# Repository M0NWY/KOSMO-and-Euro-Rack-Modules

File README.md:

# KOSMO-and-Euro-Rack-Modules
A backup place for my module designs / build instructions.

555 Techno Kick modules and or PCB and Panels available here : https://www.etsy.com/uk/shop/NewysModules

Demo video here :  https://youtu.be/yIHIAyrZvMU

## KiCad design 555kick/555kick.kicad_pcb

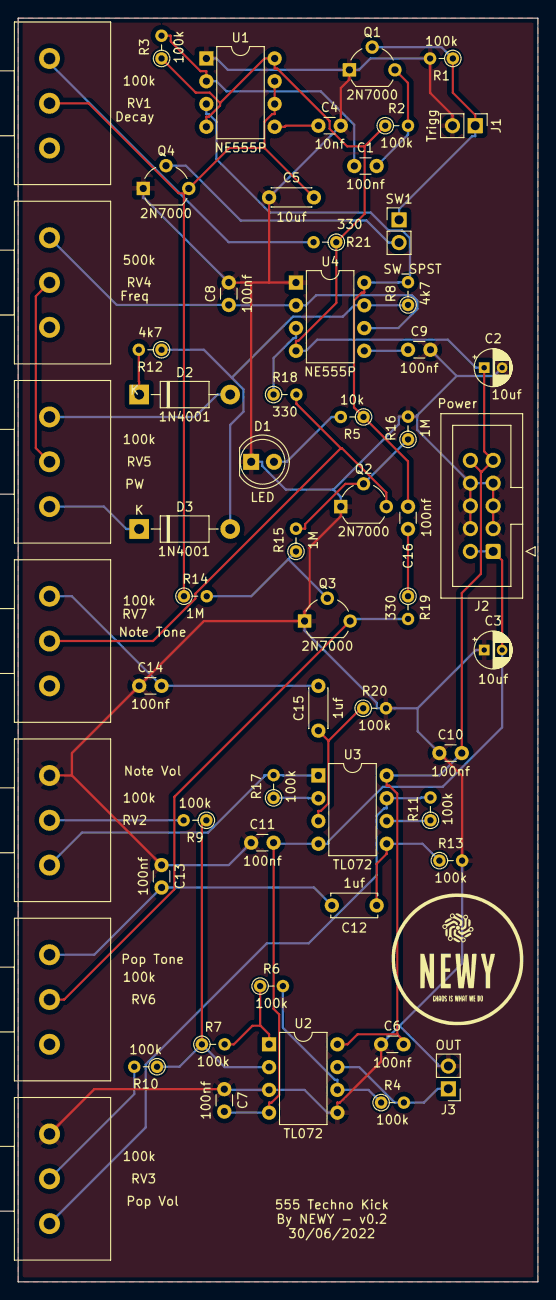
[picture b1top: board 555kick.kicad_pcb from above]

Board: 2 copper layers, 58.0 x 141.0 mm, 59 parts (0 on the bottom side), 39 nets.

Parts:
C1, C6, C7, C8, C9, C10, C11, C13, C14, C16: 100nf; C_Disc_D3.0mm_W1.6mm_P2.50mm
C2, C3: 10uf; CP_Radial_D4.0mm_P2.00mm
C4: 10nf; C_Disc_D3.0mm_W1.6mm_P2.50mm
C5: 10uf; C_Disc_D4.3mm_W1.9mm_P5.00mm
C12: 1uf; C_Disc_D5.0mm_W2.5mm_P5.00mm
C15: 1uf; C_Disc_D4.3mm_W1.9mm_P5.00mm
D1: LED; LED_D5.0mm
D2, D3: 1N4001; D_DO-41_SOD81_P10.16mm_Horizontal
J1: Trigg; PinHeader_1x02_P2.54mm_Vertical
J2: Power; IDC-Header_2x05_P2.54mm_Vertical
J3: OUT; PinHeader_1x02_P2.54mm_Vertical
Q1, Q2, Q3, Q4: 2N7000; TO-92_Wide
R1, R2, R3, R4, R6, R7, R9, R10, R11, R13, R17, R20: 100k; R_Axial_DIN0204_L3.6mm_D1.6mm_P2.54mm_Vertical
R5: 10k; R_Axial_DIN0204_L3.6mm_D1.6mm_P2.54mm_Vertical
R8, R12: 4k7; R_Axial_DIN0204_L3.6mm_D1.6mm_P2.54mm_Vertical
R14, R15, R16: 1M; R_Axial_DIN0204_L3.6mm_D1.6mm_P2.54mm_Vertical
R18, R19, R21: 330; R_Axial_DIN0204_L3.6mm_D1.6mm_P2.54mm_Vertical
RV1, RV2, RV3, RV5, RV6, RV7: 100k; Potentiometer_Alps_RK163_Single_Horizontal
RV4: 500k; Potentiometer_Alps_RK163_Single_Horizontal
SW1: SW_SPST; PinHeader_1x02_P2.54mm_Vertical
U1, U4: NE555P; DIP-8_W7.62mm
U2, U3: TL072; DIP-8_W7.62mm

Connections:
+12V: C2.1, C6.2, C10.2, J2.9, J2.10, R2.1, R3.1, R21.1, U1.4 (R), U1.8 (VCC), U2.8 (V+), U3.8 (V+), U4.4 (R)
-12V: C3.2, C7.2, C11.2, J2.1, J2.2, U2.4 (V-), U3.4 (V-)
GND: C2.2, C3.1, C4.2, C5.1, C6.1, C7.1, C8.2, C9.2, C10.1, C11.1, C13.1, C14.1, D1.1 (K), J1.2, J2.3, J2.4, J2.5, J2.6, J2.7, J2.8, J3.2, Q1.1 (S), Q2.1 (S), Q3.1 (S), Q4.1 (S), R1.2, R13.2, R16.2, R20.2, RV2.1, RV3.1, U1.1 (GND), U2.3 (+), U2.5 (+), U4.1 (GND)
unnamed: C1.1, R3.2, U1.2 (TR)
unnamed: C1.2, Q1.3 (D), R2.2
unnamed: C4.1, U1.5 (CV)
unnamed: C5.2, Q4.3 (D), R14.1, RV1.2, U1.6 (THR), U1.7 (DIS)
unnamed: C8.1, RV4.1, U4.2 (TR), U4.6 (THR)
unnamed: C9.1, U4.5 (CV)
unnamed: C12.1, R13.1, U3.5 (+)
unnamed: C12.2, C13.2, RV6.1
unnamed: C14.2, C15.2, RV7.1
unnamed: C15.1, R20.1, U3.3 (+)
unnamed: C16.1, R19.1
unnamed: C16.2, R5.1, R8.2, U1.3 (Q), U4.8 (VCC)
unnamed: D1.2 (A), R5.2
unnamed: D2.1 (K), R12.2
unnamed: D2.2 (A), RV5.1
unnamed: D3.1 (K), RV5.3
unnamed: D3.2 (A), R8.1, R12.1, U4.7 (DIS)
unnamed: J1.1, Q1.2 (G), R1.1, SW1.1 (A)
unnamed: J3.1, R4.2, U2.7
unnamed: Q2.2 (G), R15.2, R16.1
unnamed: Q2.3 (D), R18.2, RV7.2
unnamed: Q3.2 (G), R14.2, R15.1
unnamed: Q3.3 (D), R19.2, RV6.2
unnamed: Q4.2 (G), SW1.2 (B)
unnamed: R4.1, R6.2, U2.6 (-)
unnamed: R6.1, R7.2, U2.1
unnamed: R9.2, RV2.2
unnamed: R7.1, R9.1, R10.1, U2.2 (-)
unnamed: R10.2, RV3.2
unnamed: R11.1, U3.6 (-)
unnamed: R11.2, RV3.3, U3.7
unnamed: R17.1, U3.2 (-)
unnamed: R17.2, RV2.3, U3.1
unnamed: R18.1, U4.3 (Q)
unnamed: R21.2, RV1.1
unnamed: RV4.2, RV5.2
